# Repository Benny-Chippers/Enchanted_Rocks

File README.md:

# Enchanted\_Rocks

The dev board PCB for ECE 44x team 9 is in FPGA\_DevBoard.
  The PCB file that was printed & assembled is in ".._V1".

The Northbridge/Memory Block PCB is in memory\_block\_v3.

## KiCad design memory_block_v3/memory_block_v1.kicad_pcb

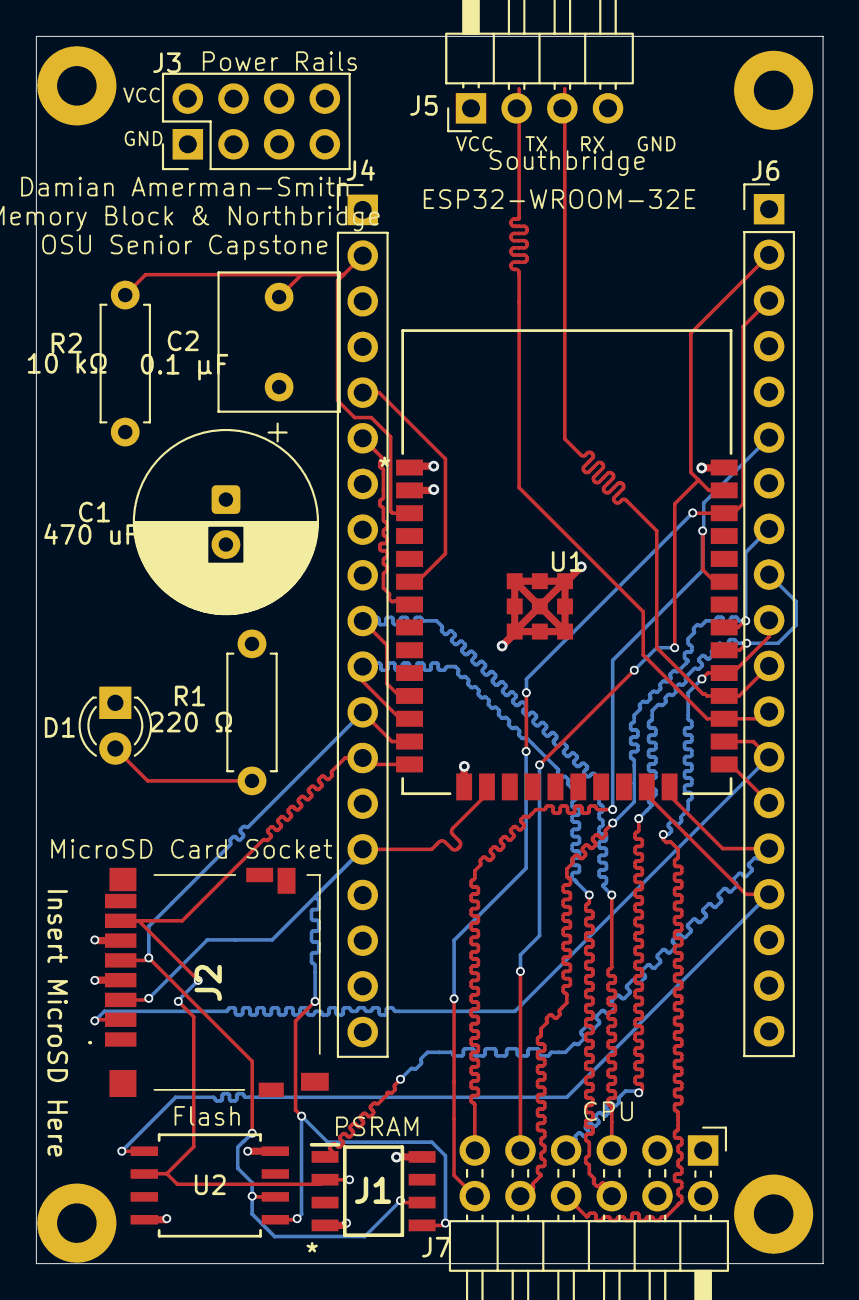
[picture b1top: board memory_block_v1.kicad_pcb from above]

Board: 4 copper layers, 43.8 x 68.2 mm, 18 parts (0 on the bottom side), 24 nets.

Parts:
C1: 470 uF; CP_Radial_D10.0mm_P2.50mm
C2: 0.1 μF; C_Rect_L7.5mm_W6.5mm_P5.00mm
D1: LED; LED_D3.0mm
H1, H2, H3, H4: MountingHole_Pad; MountingHole_2.2mm_M2_Pad
J1: 4677; SOIC127P600X175-8N
J2: DM3D-SF; DM3DSF
J3: Conn_02x04_Odd_Even; PinHeader_2x04_P2.54mm_Vertical
J4, J6: Conn_01x19; PinHeader_1x19_P2.54mm_Vertical
J5: Conn_01x04; PinHeader_1x04_P2.54mm_Horizontal
J7: Conn_02x06_Top_Bottom; PinHeader_2x06_P2.54mm_Horizontal
R1: 220 Ω; R_Axial_DIN0207_L6.3mm_D2.5mm_P7.62mm_Horizontal
R2: 10 kΩ; R_Axial_DIN0207_L6.3mm_D2.5mm_P7.62mm_Horizontal
U1: ESP32-WROOM-32E-N8; ESP32­WROOM­32E_EXP
U2: W25Q128JVSIQ TR; SOIC_208MIL_WIN

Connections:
/<NO NET>: J4.3, J4.4, J4.7, J4.8, J4.9, J4.16, J4.17, J4.18, J4.19, J6.4, J6.5, J6.17, J6.18, J6.19
BOOT: J6.14, U1.25 (IO0)
CPU_IO0: J4.10, J7.5, U1.11 (IO26)
CPU_IO1: J4.11, J7.6, U1.12 (IO27)
EN: C2.1, J4.2, R2.2, U1.3 (EN)
GND: C1.2, C2.2, D1.1 (K), H1.1, H2.1, H3.1, H4.1, J1.4 (VSS), J2.6 (VSS), J3.1, J3.3, J3.5, J3.7, J4.14, J5.4, J6.1, J6.7, J7.3, J7.4, U1.1 (GND), U1.15 (GND), U1.38 (GND), U1.39 (GND), U1.40 (GND), U1.41 (GND), U1.42 (GND), U1.43 (GND), U1.44 (GND), U1.45 (GND), U1.46 (GND), U1.47 (GND), U2.4 (GND)
HSPI_CLK: J1.6 (SCLK), J2.5 (CLK), J4.12, U1.13 (IO14), U2.6 (CLK)
HSPI_CS_FL: J6.16, U1.23 (IO15), U2.1 (/CS)
HSPI_CS_PS: J1.1 (CE#), J6.15, U1.24 (IO2)
HSPI_CS_SD: J2.2 (CD/DAT3), J6.13, U1.26 (IO4)
HSPI_MISO: J1.2 (SO/SIO[1]), J2.7 (DAT0), J4.13, U1.14 (IO12), U2.2 (DO(IO1))
HSPI_MOSI: J1.5 (SI/SIO[0]), J2.3 (CMD), J4.15, U1.16 (IO13), U2.5 (DI(IO0))
unnamed: D1.2 (A), R1.2
P_RX: J4.6, U1.7 (IO35)
P_TX: J4.5, U1.6 (IO34)
SB_RX: J5.3, J6.11, U1.28 (IO17)
SB_TX: J5.2, J6.12, U1.27 (IO16)
VCC: C1.1, J1.8 (VCC), J2.4 (VDD), J3.2, J3.4, J3.6, J3.8, J4.1, J5.1, R1.1, R2.1, U1.2 (3V3), U2.8 (VCC)
VSPI_CLK: J6.9, J7.7, U1.30 (IO18)
VSPI_CS: J6.10, J7.8, U1.29 (IO5)
VSPI_D0: J6.2, J7.9, U1.37 (IO23)
VSPI_D1: J6.8, J7.10, U1.31 (IO19)
VSPI_D2: J6.6, J7.11, U1.33 (IO21)
VSPI_D3: J6.3, J7.12, U1.36 (IO22)

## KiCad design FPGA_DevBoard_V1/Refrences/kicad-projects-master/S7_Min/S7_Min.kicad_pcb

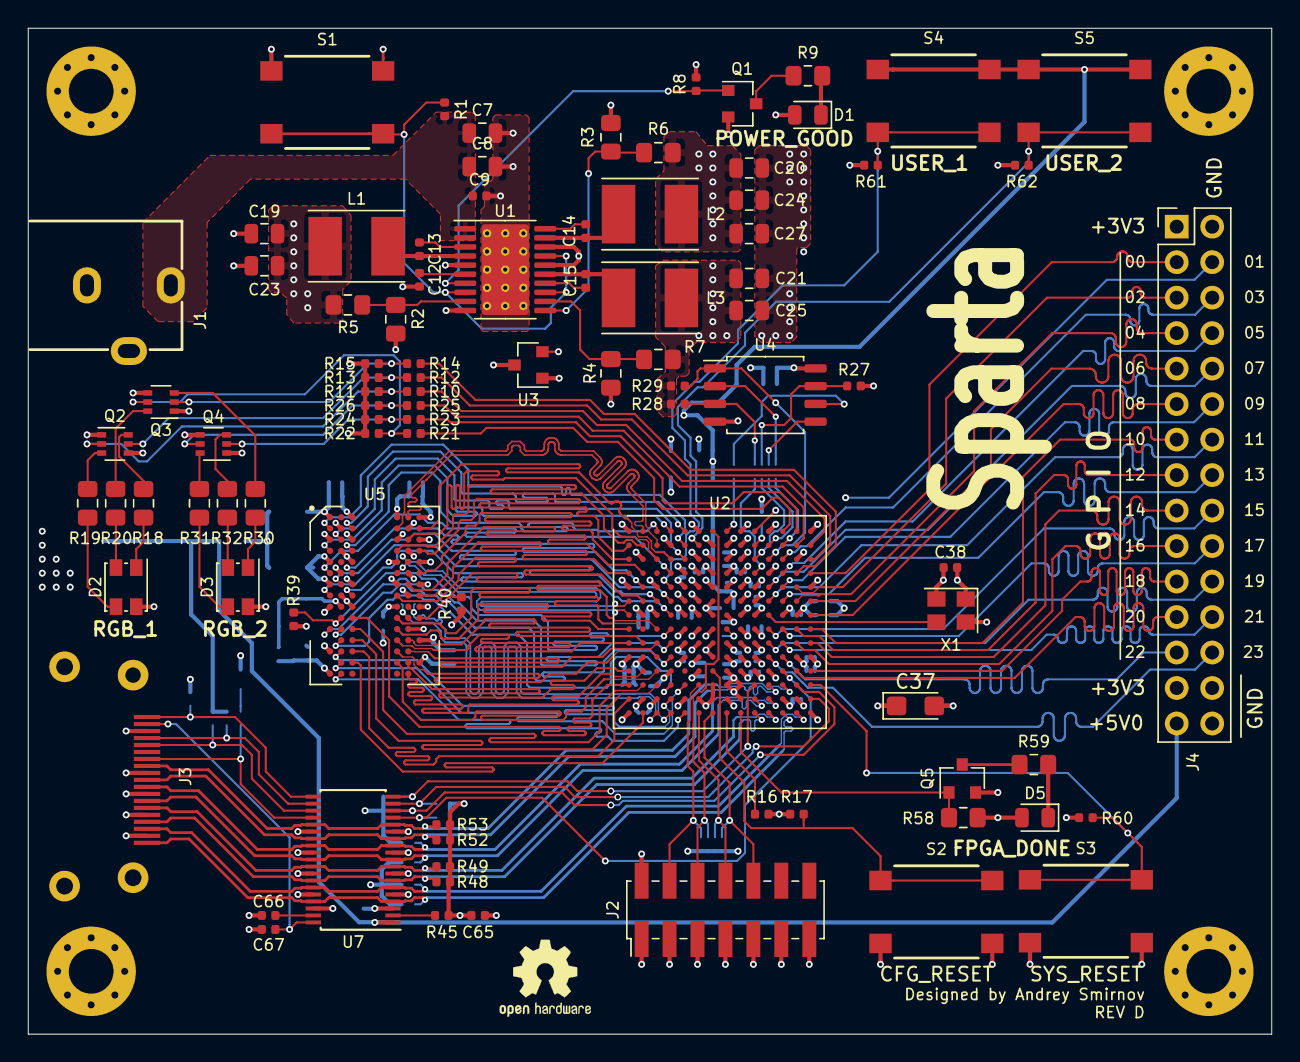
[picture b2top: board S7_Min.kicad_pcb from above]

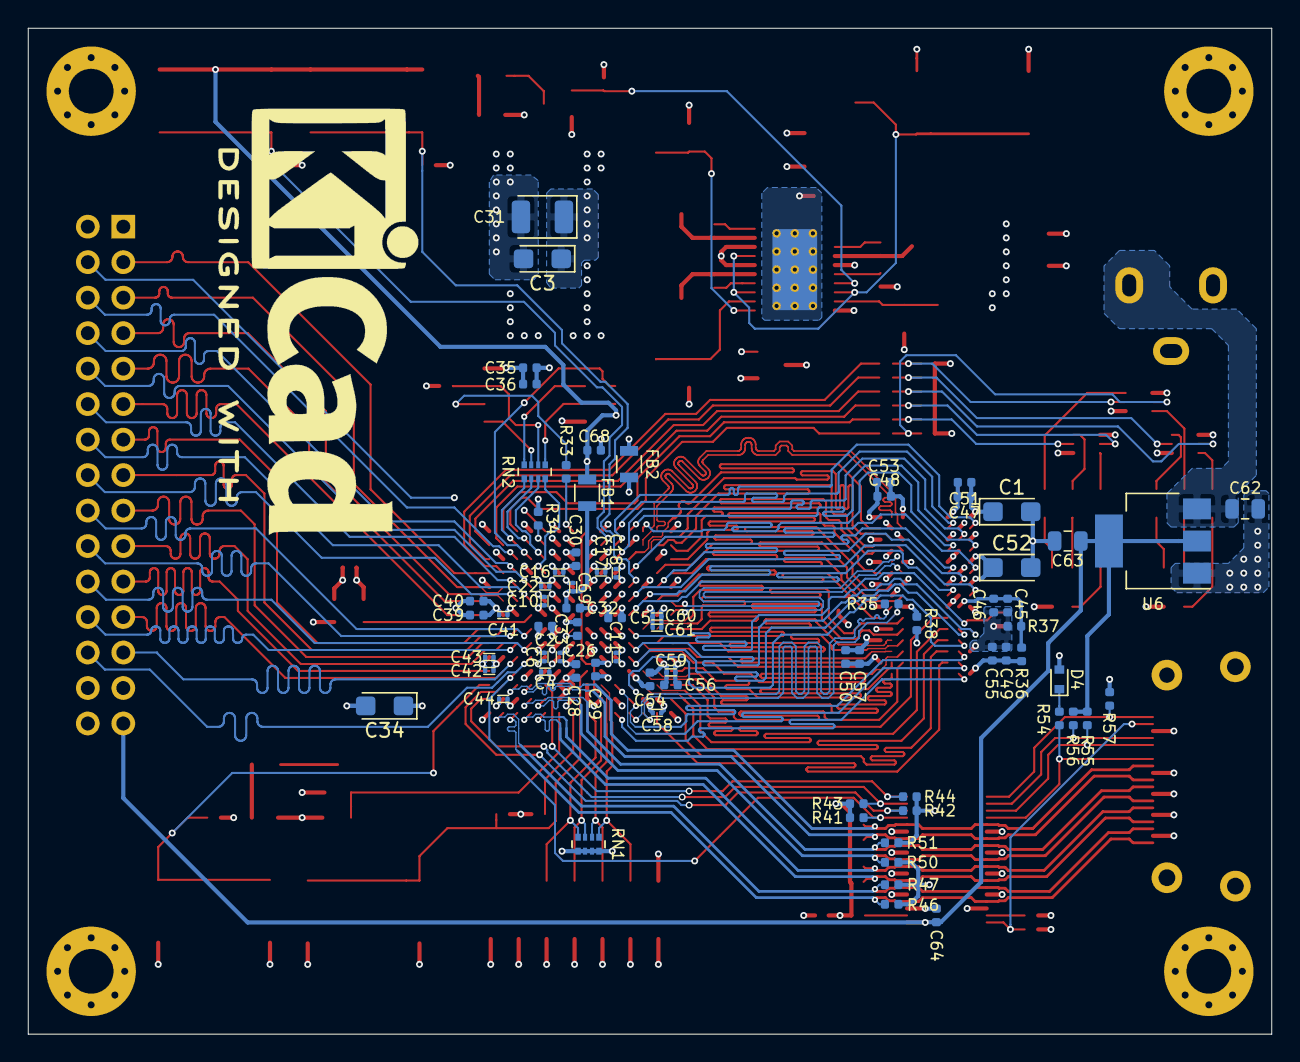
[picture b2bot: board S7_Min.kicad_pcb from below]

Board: 4 copper layers, 89.0 x 72.0 mm, 169 parts (74 on the bottom side), 164 nets.

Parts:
C1, C3, C34, C37, C52: 47 uF; CP_EIA-3216-18_Kemet-A
C2, C5, C28, C29, C30, C39, C40, C54, C56, C68: 4.7 uF; C_0402_1005Metric
C4, C6, C10, C11, C16, C17, C18, C22, C26, C41, C42, C43, C44, C58, C59, C60, C61, C69: 0.47 uF; C_0201_0603Metric
C7, C8, C62: 10 uF; C_0805_2012Metric
C9, C13, C14, C15, C32, C33, C35, C38, C45, C47, C48, C49, C50, C64, C65, C66, C67: 0.1 uF; C_0402_1005Metric
C12, C36, C51, C53, C55, C57: 1 uF; C_0402_1005Metric
C19, C20, C21, C23, C24, C25, C27, C63: 22 uF; C_0805_2012Metric
C31: 100 uF; CP_EIA-3528-15_AVX-H
C46: 10 nF; C_0402_1005Metric
D1: POWER_GOOD; LED_0805_2012Metric
D2, D3: LED_RAGB; LED_Kingbright_AAA3528ESGCT
D4: BAS16XV2T1G; D_SOD-523
D5: FPGA_DONE; LED_0805_2012Metric
FB1, FB2: 600R; L_0805
H1, H2, H3, H4: MountingHole_Pad; MountingHole_3.2mm_M3_Pad_Via
J1: Barrel_Jack_Switch; PJ_102B
J2: XILINX_JTAG; PinHeader_2x07_P2.00mm_Vertical_SMD
J3: HDMI_A; hdmi_type_a_10029449-111RLF
J4: Conn_02x15_Odd_Even; PinHeader_2x15_P2.54mm_Vertical
L1, L2, L3: 2.2 uH; L_Taiyo-Yuden_NR-50xx_HandSoldering
Q1, Q5: DMN2020L; SOT-23
Q2, Q3, Q4: DMN63D8LDW; SOT-363_SC-70-6
R1, R8, R44: 100K; R_0402_1005Metric
R2, R3, R4: 2.2K; R_0805_2012Metric_Pad1.15x1.40mm_HandSolder
R5: 3.0K; R_0805_2012Metric_Pad1.15x1.40mm_HandSolder
R6, R9, R18, R30, R59: 680; R_0805_2012Metric_Pad1.15x1.40mm_HandSolder
R7: 7.36K; R_0805_2012Metric_Pad1.15x1.40mm_HandSolder
R10, R12, R14, R21, R23, R25, R55, R56: 2.2K; R_0402_1005Metric
R11, R13, R15, R22, R24, R26, R45, R57: 10K; R_0402_1005Metric
R16, R17, R27, R28, R29, R34, R38, R39, R40, R60, R61, R62: 4.75K; R_0402_1005Metric
R19, R20, R31, R32, R58: 330; R_0805_2012Metric_Pad1.15x1.40mm_HandSolder
R33, R46, R47, R48, R49, R50, R51, R52, R53: 49.9; R_0402_1005Metric
R35: 100; R_0402_1005Metric
R36, R37: 1.0K; R_0402_1005Metric
R41, R42, R43: 47K; R_0402_1005Metric
R54: 27K; R_0402_1005Metric
RN1: 10K; R_Array_Convex_4x0402
RN2: 49.9; R_Array_Convex_4x0402
S1: PWR_OFF; B3FS_1010P
S2: CFG_RESET; B3FS_1010P
S3: SYS_RESET; B3FS_1010P
S4: USER_1; B3FS_1010P
S5: USER_2; B3FS_1010P
U1: TPS65581; HTSSOP-20-1EP_4.4x6.5mm_P0.65mm_EP3.4x6.5mm_Mask2.75x3.43mm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
U2: XC7S50-FTGB196; Xilinx_FTGB196
U3: REF3012; SOT-23
U4: QSPI_Flash_SOIC8; SOIC-8_5.275x5.275mm_P1.27mm
U5: MT47H128M16XX; BGA-84_9x15_9.0x12.5mm
U6: AZ1117-5.0; SOT-223-3_TabPin2
U7: TPD12S521; TSSOP-38_4.4x9.7mm_P0.5mm
X1: DSC61XX; Oscillator_SMD_Abracon_ASE-4Pin_3.2x2.5mm

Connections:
+1V0: C3.1, C5.1, C11.1, C16.1, C17.1, C18.1, C20.1, C22.1, C24.1, C26.1, C27.1, C28.1, C29.1, C30.1, C31.1, L2.2, R6.1, U2.D6, U2.D8, U2.E5, U2.E7, U2.E9, U2.F6, U2.G5, U2.G9, U2.H6, U2.J5, U2.J9, U2.K6, U2.K8
+1V8: C1.1, C2.1, C4.1, C6.1, C10.1, C19.1, C23.1, C47.1, C48.1, C49.1, C50.1, C51.1, C52.1, C53.1, C54.1, C55.1, C56.1, C57.1, C58.1, C59.1, C60.1, C61.1, C68.1, FB1.2, L1.2, R5.1, R36.2, S4.1, S4.2, S5.1, S5.2, U2.F10, U2.G2, U2.H10, U2.K2, U2.K10, U2.L9, U2.N2, U5.A1, U5.A9, U5.C1, U5.C3, U5.C7, U5.C9, U5.E1, U5.E9, U5.G1, U5.G3, U5.G7, U5.G9, U5.J1, U5.J9, U5.M9, U5.R1
+1V8A: C32.1, C69.1, FB1.1, U2.F8
+3V3: C21.1, C25.1, C34.1, C35.1, C36.1, C37.1, C38.1, C39.1, C40.1, C41.1, C42.1, C43.1, C44.1, C65.1, D1.2, D2.2, D3.2, D4.2, D5.2, J2.2, J4.1, J4.27, L3.2, R7.1, R8.2, R16.2, R17.2, R27.2, R28.2, R29.2, R34.1, R41.1, R42.1, R43.1, R44.1, R45.2, R46.1, R47.1, R48.1, R49.1, R50.1, R51.1, R52.1, R53.1, R58.2, R60.1, RN1.5, RN1.6, RN1.7, RN1.8, U2.G13, U2.K13, U2.M7, U2.N6, U2.N7, U2.N8, U2.N13, U3.1, U4.8, X1.1, X1.4
+5V: C63.1, C64.1, J4.29, R55.2, R56.2, U6.2, U7.1
+12V: C7.1, C8.1, C9.1, C62.2, J1.1, R1.2, U1.1, U1.2, U6.3
/Bank0_14/FPGA_DONE: Q5.1, R58.1, U2.P9
/Bank0_14/FPGA_PUDC: R34.2, U2.B10
/Bank0_14/INIT_B: R16.1, U2.P8
/Bank0_14/JTAG_TCK: J2.6, RN1.2, U2.A7
/Bank0_14/JTAG_TDI: J2.10, RN1.4, U2.P7
/Bank0_14/JTAG_TDO: J2.8, RN1.3, U2.P6
/Bank0_14/JTAG_TMS: J2.4, RN1.1, U2.M6
/Bank0_14/PROGRAM_B: R17.1, S2.1, S2.2, U2.L7
/Bank0_14/RGB1_B: R14.2, U2.D13
/Bank0_14/RGB1_G: R12.2, U2.C14
/Bank0_14/RGB1_R: R10.2, U2.B14
/Bank0_14/RGB2_B: R25.2, U2.B13
/Bank0_14/RGB2_G: R23.2, U2.A13
/Bank0_14/RGB2_R: R21.2, U2.A12
/Bank0_14/SPI_CS: R29.1, U2.C11, U4.1
/Bank0_14/SPI_DQ0: RN2.3, U4.5
/Bank0_14/SPI_DQ1: RN2.4, U4.2
/Bank0_14/SPI_DQ2: R28.1, RN2.1, U4.3
/Bank0_14/SPI_DQ3: R27.1, RN2.2, U4.7
/Bank0_14/SPI_F_DQ0: RN2.6, U2.B11
/Bank0_14/SPI_F_DQ1: RN2.5, U2.B12
/Bank0_14/SPI_F_DQ2: RN2.8, U2.D10
/Bank0_14/SPI_F_DQ3: RN2.7, U2.C10
/Bank0_14/SPI_F_SCLK: R33.1, U2.A8
/Bank0_14/SPI_SCLK: R33.2, U4.6
/Bank0_14/SYSCLK: U2.G11, X1.3
/Bank0_14/SYSRESET: R60.2, S3.1, S3.2, U2.M14
/Bank34/DDR2_A0: U2.J2, U5.M8
/Bank34/DDR2_A1: U2.M3, U5.M3
/Bank34/DDR2_A2: U2.J1, U5.M7
/Bank34/DDR2_A3: U2.N4, U5.N2
/Bank34/DDR2_A4: U2.J3, U5.N8
/Bank34/DDR2_A5: U2.N1, U5.N3
/Bank34/DDR2_A6: U2.K3, U5.N7
/Bank34/DDR2_A7: U2.M5, U5.P2
/Bank34/DDR2_A8: U2.L1, U5.P8
/Bank34/DDR2_A9: U2.P2, U5.P3
/Bank34/DDR2_A10: U2.M4, U5.M2
/Bank34/DDR2_A11: U2.L3, U5.P7
/Bank34/DDR2_A12: U2.P5, U5.R2
/Bank34/DDR2_A13: U2.L2, U5.R8
/Bank34/DDR2_BA0: U2.K4, U5.L2
/Bank34/DDR2_BA1: U2.M2, U5.L3
/Bank34/DDR2_BA2: U2.J4, U5.L1
/Bank34/DDR2_CAS: U2.H1, U5.L7
/Bank34/DDR2_CK+: R35.1, U2.P4, U5.J8
/Bank34/DDR2_CK-: R35.2, U2.P3, U5.K8
/Bank34/DDR2_CKE: R39.2, U2.H4, U5.K2
/Bank34/DDR2_DM0: U2.E2, U5.F3
/Bank34/DDR2_DM1: U2.A5, U5.B3
/Bank34/DDR2_DQ0: U2.D2, U5.G8
/Bank34/DDR2_DQ1: U2.F4, U5.G2
/Bank34/DDR2_DQ2: U2.F2, U5.H7
/Bank34/DDR2_DQ3: U2.G4, U5.H3
/Bank34/DDR2_DQ4: U2.F3, U5.H1
/Bank34/DDR2_DQ5: U2.D1, U5.H9
/Bank34/DDR2_DQ6: U2.D4, U5.F1
/Bank34/DDR2_DQ7: U2.C1, U5.F9
/Bank34/DDR2_DQ8: U2.C3, U5.C8
/Bank34/DDR2_DQ9: U2.C5, U5.C2
/Bank34/DDR2_DQ10: U2.B2, U5.D7
/Bank34/DDR2_DQ11: U2.A3, U5.D3
/Bank34/DDR2_DQ12: U2.A4, U5.D1
/Bank34/DDR2_DQ13: U2.B1, U5.D9
/Bank34/DDR2_DQ14: U2.B5, U5.B1
/Bank34/DDR2_DQ15: U2.C4, U5.B9
/Bank34/DDR2_DQS0+: U2.G1, U5.F7
/Bank34/DDR2_DQS0-: U2.F1, U5.E8
/Bank34/DDR2_DQS1+: U2.B3, U5.B7
/Bank34/DDR2_DQS1-: U2.A2, U5.A8
/Bank34/DDR2_ODT: R40.2, U2.H3, U5.K9
/Bank34/DDR2_RAS: U2.H2, U5.K7
/Bank34/DDR2_WE: U2.M1, U5.K3
/Bank34/USER_1: R61.1, S4.3, S4.4, U2.E4
/Bank34/USER_2: R62.1, S5.3, S5.4, U2.B6
/Externals/HDMI_C_5V: C67.2, J3.18, U7.38
/Externals/HDMI_C_CEC: J3.13, R54.1, U7.23
/Externals/HDMI_C_HPD: J3.19, R57.1, U7.20
/Externals/HDMI_C_SCL: J3.15, R55.1, U7.22
/Externals/HDMI_C_SDA: J3.16, R56.1, U7.21
/Power/PGOOD: Q1.1, R8.1, U1.7
/Power/SW1: C13.1, L1.1, U1.4
/Power/SW2: C14.1, L2.1, U1.19
/Power/SW3: C15.1, L3.1, U1.15
ADC_REF: C33.1, U2.H8, U3.2
GND: C1.2, C2.2, C3.2, C4.2, C5.2, C6.2, C7.2, C8.2, C9.2, C10.2, C11.2, C12.2, C16.2, C17.2, C18.2, C19.2, C20.2, C21.2, C22.2, C23.2, C24.2, C25.2, C26.2, C27.2, C28.2, C29.2, C30.2, C31.2, C34.2, C35.2, C36.2, C37.2, C38.2, C39.2, C40.2, C41.2, C42.2, C43.2, C44.2, C45.2, C46.2, C47.2, C48.2, C49.2, C50.2, C51.2, C52.2, C53.2, C54.2, C55.2, C56.2, C57.2, C58.2, C59.2, C60.2, C61.2, C62.1, C63.2, C64.2, C65.2, C66.1, C67.1, C68.2, C69.2, FB2.2, H1.1, H2.1, H3.1, H4.1, J1.2, J2.1, J2.3, J2.5, J2.7, J2.9, J2.11, J2.13, J3.2, J3.5, J3.8, J3.11, J3.17, J3.SH, J4.2, J4.28, J4.30, Q1.2, Q2.1, Q2.4, Q3.1, Q3.4, Q4.1, Q4.4, Q5.2, R2.2, R3.2, R4.2, R11.2, R13.2, R15.2, R22.2, R24.2, R26.2, R37.1, R38.1, R39.1, R40.1, R57.2, R61.2, R62.2, S1.1, S1.2, S2.3, S2.4, S3.3, S3.4, U1.5, U1.10, U1.16, U1.18, U1.21, U2.A1, U2.A6, U2.A9, U2.A11, U2.A14, U2.B4, U2.B7, U2.B8, U2.B9, U2.C2, U2.C6, U2.C7, U2.C8, U2.C9, U2.C13, U2.D5, U2.D7, U2.D9, U2.D11, U2.E1, U2.E3, U2.E6, U2.E8, U2.E10, U2.E14, U2.F5, U2.F9, U2.G3, U2.G6, U2.G10, U2.G12, U2.H5, U2.H9, U2.J6, U2.J7, U2.J8, U2.J10, U2.K1, U2.K5, U2.K7, U2.K9, U2.K14, U2.L4, U2.L6, U2.L8, U2.L10, U2.L11, U2.M8, U2.M9, U2.N3, U2.N5, U2.N9, U2.N12, U2.P1, U2.P14, U3.3, U4.4, U5.A3, U5.A7, U5.B2, U5.B8, U5.D2, U5.D8, U5.E3, U5.E7, U5.F2, U5.F8, U5.H2, U5.H8, U5.J3, U5.J7, U5.N1, U5.P9, U6.1, U7.3, U7.5, U7.8, U7.11, U7.14, U7.25, U7.28, U7.31, U7.34, U7.36, X1.2
GNDA: C32.2, C33.2, FB2.1, U2.F7, U2.G7, U2.G8, U2.H7
GPIO_0: J4.3, U2.D14
GPIO_1: J4.4, U2.A10
GPIO_2: J4.5, U2.E13
GPIO_3: J4.6, U2.C12
GPIO_4: J4.7, U2.F13
GPIO_5: J4.8, U2.D12
GPIO_6: J4.9, U2.F14
GPIO_7: J4.10, U2.E11
GPIO_8: J4.11, U2.G14
GPIO_9: J4.12, U2.E12
GPIO_10: J4.13, U2.H14
GPIO_11: J4.14, U2.F11
GPIO_12: J4.15, U2.H13
GPIO_13: J4.16, U2.F12
GPIO_14: J4.17, U2.J14
GPIO_15: J4.18, U2.H11
GPIO_16: J4.19, U2.J13
GPIO_17: J4.20, U2.H12
GPIO_18: J4.21, U2.L14
GPIO_19: J4.22, U2.J11
GPIO_20: J4.23, U2.L13
GPIO_21: J4.24, U2.J12
GPIO_22: J4.25, U2.K12
GPIO_23: J4.26, U2.K11
HDMI_CEC: R41.2, U2.L12, U7.16
HDMI_CLK+: J3.10, R52.2, U2.M11, U7.13, U7.26
HDMI_CLK-: J3.12, R53.2, U2.M12, U7.15, U7.24
HDMI_D0+: J3.7, R50.2, U2.N10, U7.10, U7.29
HDMI_D0-: J3.9, R51.2, U2.N11, U7.12, U7.27
HDMI_D1+: J3.4, R48.2, U2.P10, U7.7, U7.32
HDMI_D1-: J3.6, R49.2, U2.P11, U7.9, U7.30
HDMI_D2+: J3.1, R46.2, U2.P12, U7.4, U7.35
HDMI_D2-: J3.3, R47.2, U2.P13, U7.6, U7.33
HDMI_HPD: R44.2, U2.M10, U7.19
HDMI_SCL: R42.2, U2.M13, U7.17
HDMI_SDA: R43.2, U2.N14, U7.18
unnamed: C12.1, U1.6
unnamed: C13.2, U1.3
unnamed: C14.2, U1.20
unnamed: C15.2, U1.14
unnamed: C45.1, C46.1, R36.1, R37.2, U5.J2
unnamed: C66.2, U7.37
unnamed: D1.1, R9.2
unnamed: D2.1, R18.1
unnamed: D2.3, R19.1
unnamed: D2.4, R20.1
unnamed: D3.1, R30.1
unnamed: D3.3, R31.1
unnamed: D3.4, R32.1
unnamed: D4.1, R54.2
unnamed: D5.1, R59.2
unnamed: Q1.3, R9.1
unnamed: Q2.2, R10.1, R11.1
unnamed: Q2.3, R19.2
unnamed: Q2.5, R12.1, R13.1
unnamed: Q2.6, R18.2
unnamed: Q3.2, R14.1, R15.1
unnamed: Q3.3, R30.2
unnamed: Q3.5, R21.1, R22.1
unnamed: Q3.6, R20.2
unnamed: Q4.2, R23.1, R24.1
unnamed: Q4.3, R32.2
unnamed: Q4.5, R25.1, R26.1
unnamed: Q4.6, R31.2
unnamed: Q5.3, R59.1
unnamed: R1.1, S1.3, S1.4, U1.8, U1.13, U1.17
unnamed: R2.1, R5.2, U1.9
unnamed: R3.1, R6.2, U1.11
unnamed: R4.1, R7.2, U1.12
unnamed: R38.2, U5.L8
unnamed: R45.1, U7.2

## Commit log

2026-02-21 Moved Devboard Files
    Moved the FPGA Devboard files to GITHUB
2026-02-21 ESD UPDATE
    Updated some of the FPGA routes, Looked into the spi bus and updated the ESD on the GPIO.
2026-02-23 ESD
    Added ESD to the main USB programmer. Also added terminating resistors and test points. Also updated some planes to make sure everything was connected.
2026-02-23 FTDI
    Added EEPROM To FTDI. Updated NB SPI bus. Added Debug LEDs to FTDI chip - PWREN and SUSPEND
2026-02-23 Traces
    Just Traces
2026-02-23 Messing around with JTAG
2026-02-23 Removed Mux
2026-02-24 Updated ESD for both the USB hub outputs and GPIO output
2026-02-24 forgot to save schematic when pushing last commit
2026-02-24 updated fron and back silkscreens, additionally fixed some DRC issues
2026-02-24 added ESD to BGA and length matched it
2026-02-24 Messed around with Traces again
2026-02-24 Power Inductors
2026-02-25 Final updates
    Draft 1 Finished!
2026-02-26 Push From Laptop
    Just pushing the stuff I did on my laptop before we sent.
2026-04-04 Backup of NB/MB PCB
    Uploading NB/MB board for version control with new updates.
2026-04-05 pt1 NB/MB repairs
2026-04-05 First Draft NB/MB Schematic
    PCB has yet to be updated, but added enable strapping resistor, power LED, and power-stabilizing capacitor. Next plans are implementing these changes on a 4-layer PCB.
2026-04-05 forked kicad files to allow us to work and lookup at the same time
2026-04-06 FTDI CHIP UPDATE
    Updated all the PD stuff on the FTDI chip, also updated the USB to not be crossed, also moved the filtering caps towards the center of the chip.
2026-04-06 Start of NB/MB PCB Rework
2026-04-07 continued NB/MB pcb progress
2026-04-10 Changed header pins, redone PCB layout
    Still need to do actual trace routing, but have general components mapped out.
2026-04-11 Continued PCB Layout Edits
2026-04-11 First Draft of Signal Routing
    Need to length-match SPI traces and perhaps simplify how signals cross over each other. Also, next goal is decoration.
2026-04-12 Final (Electrical) Draft for v3
    Trace routing and length matching done. May alter silkscreens, but almost ready.
2026-04-25 Updated the NBSB IO to not go to input only, need to change this on the layout. Updated the FPGA clk to go to a positive differential signal with MCRR - need to change on layout. Updated the USB-UART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
2026-04-26 Updated the layout to remove the JTAG header, connect the proper lines for the UART, and connect the proper pins for the audio.
2026-04-28 OK I PULL UP
    Added pull up resistors to SPI CS, pull down to GPIO12, redid vga bus lines. This also might include the FPGA clock being correct? Idk if that was committed before
2026-05-01 Universal Serial Bussin it down
    Replaced the USB Hub with the new USB Hosts, added a clock reset button, moved some things on the silk screen.
2026-05-01 VGA LENGTH MATCH, LED
    Length matched the VGA, updated the GPIO to use the usb host gpio, added some leds and fixed the silkscreen more
2026-05-01 Final Final Final Lol
2026-05-01 This is V2 Ordered
